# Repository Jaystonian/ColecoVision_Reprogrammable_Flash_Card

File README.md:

# ColecoVision_Reprogrammable_Flash_Card
An opensource, reprogrammable cartridge for the ColecoVision

MODES OF USE:

A) Single flash chip
- select 32KB or 16KB rom type (J1/JP1)
- select 80-BF for typical 16KB roms, or 80-FF for 32KB roms.
- 2nd flash chip must be absent and its jumpers may be ignored.

B) Dual flash chips (32KB double memory)
- select 16KB rom type (J1/JP1)
- One chip must select 80-BF and contain an array of the lower 16KB of each 32KB rom, the other must select C0-FF and contain the upper 16KB. 
- Your roms will need to be split in half for two 16KB binary files (low and high). Then concatenated into a low file and a high file, for writing.

**NOTES**
All modes require 32KB mode for re-programming flash chips.
Re-programming also requires SW2 switches to all be OPEN and
J2/JP2 must be PROG. Revert jumper back to USE when finished.
The re-programming adapter must have the pullups for block select and a
jumper to select which flash chip to reprogram.

While in 16KB mode, single or dual chip, Address 14 (A14) in SW2 
Memory Select will be included in selecting memory. 32KB mode will
require A14 and this jumper switch will be ignored by J1/JP1 configuration,
allowing the installation of a smaller DIP switch. If you use a single, smaller
Flash chip such as the SST39SF010A (instead of the 'F04) then you do not
need switches for A18 or A17, reducing it to two toggle switches for
four 32KB roms on A15 and A16.

Dual-flash uses dual 16KB for 32KB roms, so the A14 switch is needed to address roms.

8-12KB ROMs must be right-padded to 16KB with 0's.
20-24KB ROMs must be right-padded to 32KB with 0's.

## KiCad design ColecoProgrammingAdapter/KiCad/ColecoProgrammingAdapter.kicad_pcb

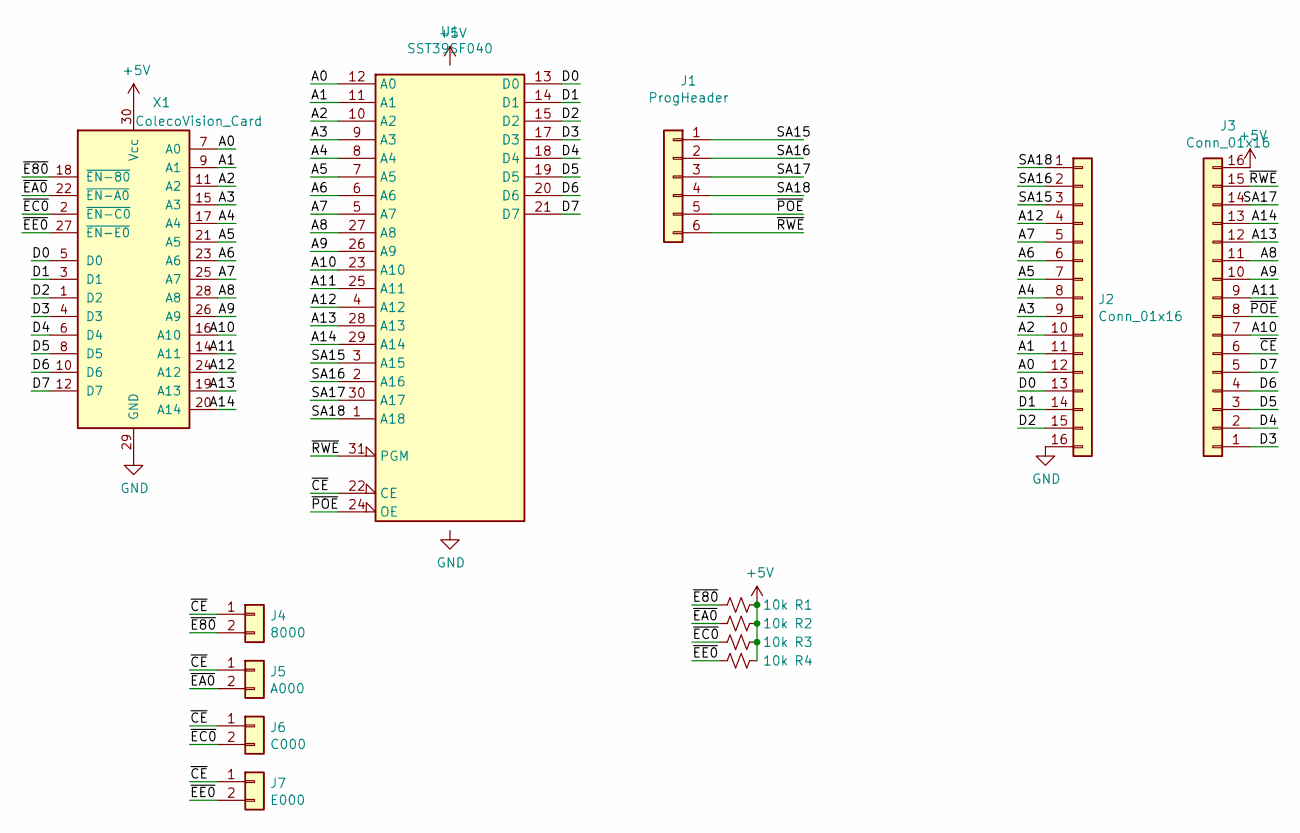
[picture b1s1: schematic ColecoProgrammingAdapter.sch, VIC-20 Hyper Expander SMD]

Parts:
J1: ProgHeader; PinSocket_1x06_P2.54mm_Vertical
J2, J3: Conn_01x16; PinHeader_1x16_P2.54mm_Vertical
J4: 8000; PinHeader_1x02_P2.54mm_Vertical
J5: A000; PinHeader_1x02_P2.54mm_Vertical
J6: C000; PinHeader_1x02_P2.54mm_Vertical
J7: E000; PinHeader_1x02_P2.54mm_Vertical
R1, R2, R3, R4: 10k; R_0805_2012Metric_Pad1.20x1.40mm_HandSolder
U1: SST39SF040; DIP-32_W15.24mm_Socket
X1: ColecoVision_Card; Coleco_CartridgeConnector

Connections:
+5V: J3.16, R1.1, R2.1, R3.1, R4.1, U1.32 (VCC), X1.30 (Vcc)
/A0: J2.12, U1.12 (A0), X1.7 (A0)
/A1: J2.11, U1.11 (A1), X1.9 (A1)
/A2: J2.10, U1.10 (A2), X1.11 (A2)
/A3: J2.9, U1.9 (A3), X1.15 (A3)
/A4: J2.8, U1.8 (A4), X1.17 (A4)
/A5: J2.7, U1.7 (A5), X1.21 (A5)
/A6: J2.6, U1.6 (A6), X1.23 (A6)
/A7: J2.5, U1.5 (A7), X1.25 (A7)
/A8: J3.11, U1.27 (A8), X1.28 (A8)
/A9: J3.10, U1.26 (A9), X1.26 (A9)
/A10: J3.7, U1.23 (A10), X1.16 (A10)
/A11: J3.9, U1.25 (A11), X1.14 (A11)
/A12: J2.4, U1.4 (A12), X1.24 (A12)
/A13: J3.12, U1.28 (A13), X1.19 (A13)
/A14: J3.13, U1.29 (A14), X1.20 (A14)
/D0: J2.13, U1.13 (D0), X1.5 (D0)
/D1: J2.14, U1.14 (D1), X1.3 (D1)
/D2: J2.15, U1.15 (D2), X1.1 (D2)
/D3: J3.1, U1.17 (D3), X1.4 (D3)
/D4: J3.2, U1.18 (D4), X1.6 (D4)
/D5: J3.3, U1.19 (D5), X1.8 (D5)
/D6: J3.4, U1.20 (D6), X1.10 (D6)
/D7: J3.5, U1.21 (D7), X1.12 (D7)
/SA15: J1.1, J2.3, U1.3 (A15)
/SA16: J1.2, J2.2, U1.2 (A16)
/SA17: J1.3, J3.14, U1.30 (A17)
/SA18: J1.4, J2.1, U1.1 (A18)
/~CE: J3.6, J4.1, J5.1, J6.1, J7.1, U1.22 (CE)
/~E80: J4.2, R1.2, X1.18 (~EN-80)
/~EA0: J5.2, R2.2, X1.22 (~EN-A0)
/~EC0: J6.2, R3.2, X1.2 (~EN-C0)
/~EE0: J7.2, R4.2, X1.27 (~EN-E0)
/~POE: J1.5, J3.8, U1.24 (OE)
/~RWE: J1.6, J3.15, U1.31 (PGM)
GND: J2.16, U1.16 (GND), X1.29 (GND)

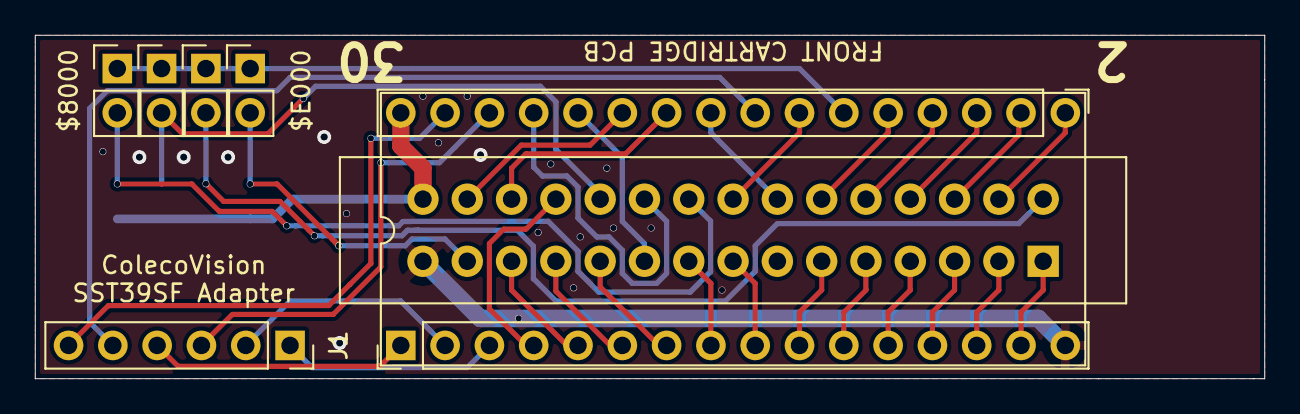
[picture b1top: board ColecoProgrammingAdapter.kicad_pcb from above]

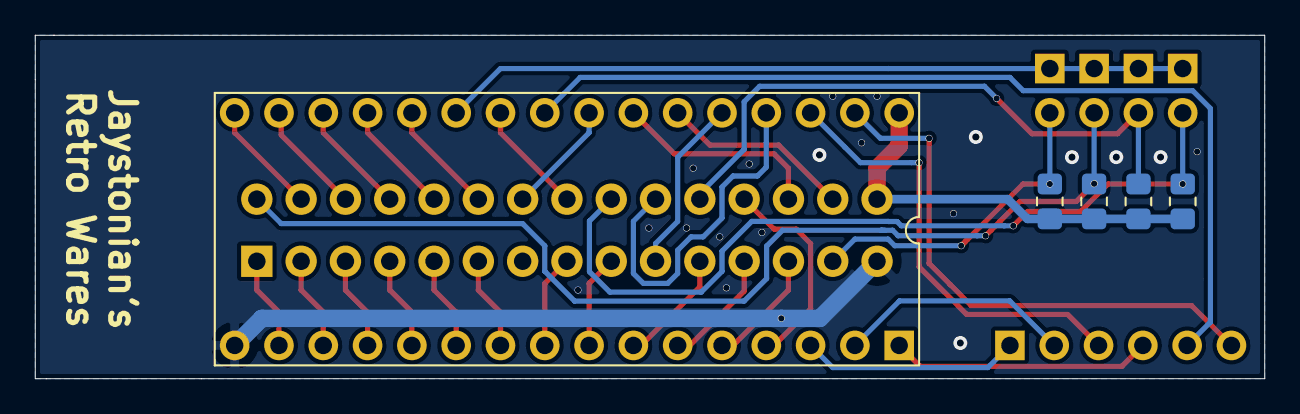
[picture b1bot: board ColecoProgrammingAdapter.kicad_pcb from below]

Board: 2 copper layers, 70.5 x 19.7 mm, 12 parts (5 on the bottom side), 36 nets.

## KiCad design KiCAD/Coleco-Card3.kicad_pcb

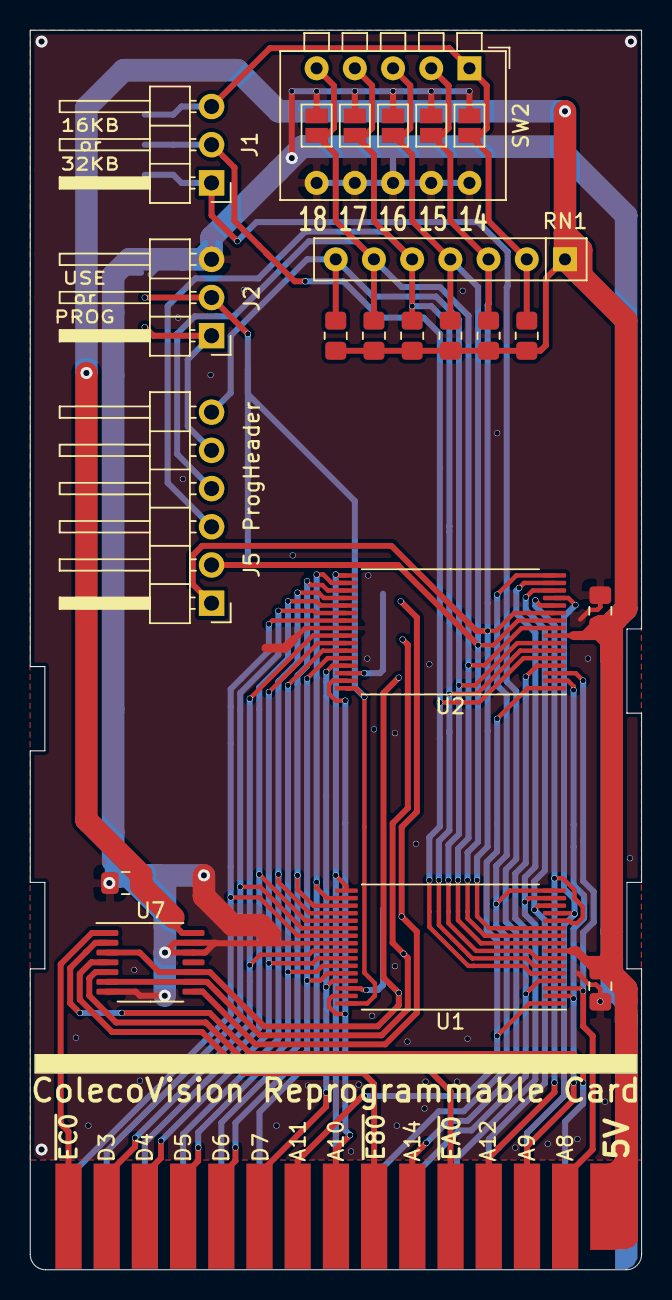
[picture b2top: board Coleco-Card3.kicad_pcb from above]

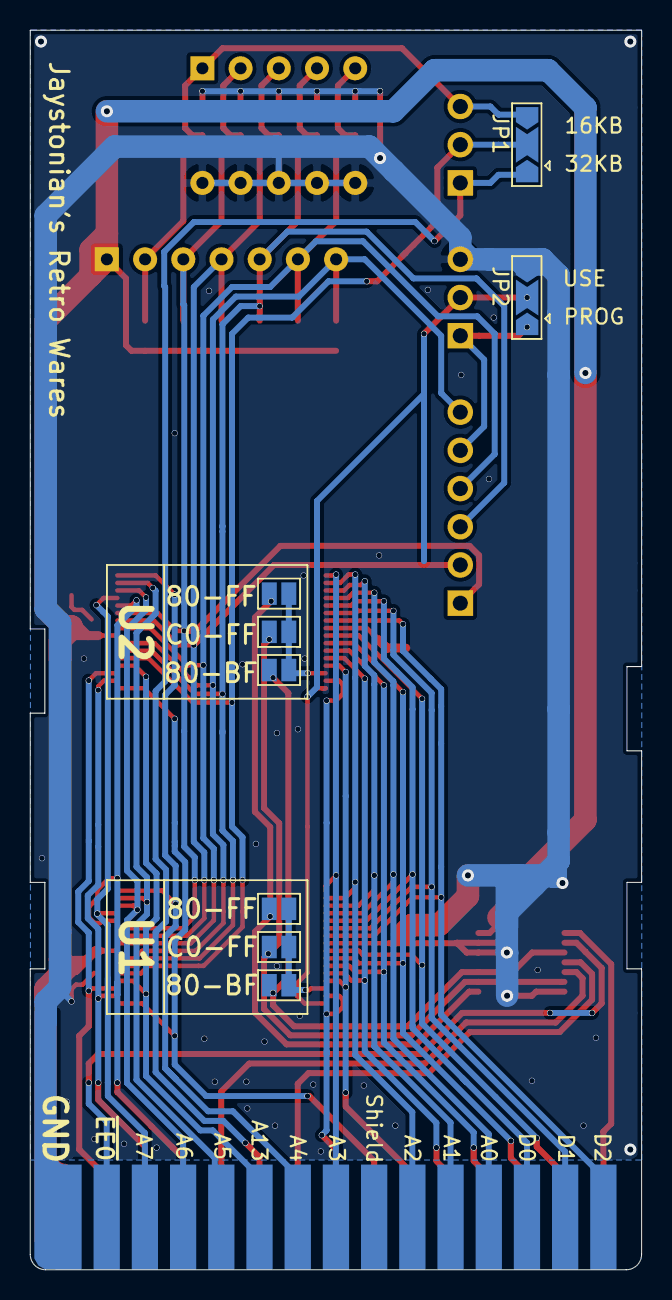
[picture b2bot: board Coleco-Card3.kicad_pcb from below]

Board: 2 copper layers, 40.6 x 82.4 mm, 31 parts (8 on the bottom side), 43 nets.

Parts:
C1, C2, C3: 0.1u; C_0805_2012Metric_Pad1.18x1.45mm_HandSolder
J1: 32KB_or_16KB; PinHeader_1x03_P2.54mm_Horizontal
J2: Prog_or_Use; PinHeader_1x03_P2.54mm_Horizontal
J5: Prog Header; PinHeader_1x06_P2.54mm_Horizontal
JP1: 32KB or 16KB; SolderJumper-3_P2.0mm_Open_TrianglePad1.0x1.5mm
JP2: Prog or Use; SolderJumper-3_P2.0mm_Open_TrianglePad1.0x1.5mm
JP3: SA14; SolderJumper-2_P1.3mm_Open_Pad1.0x1.5mm
JP4: SA15; SolderJumper-2_P1.3mm_Open_Pad1.0x1.5mm
JP5: SA16; SolderJumper-2_P1.3mm_Open_Pad1.0x1.5mm
JP6, JP14: SJE01; SolderJumper-2_P1.3mm_Open_Pad1.0x1.5mm
JP7, JP15: SJE23; SolderJumper-2_P1.3mm_Open_Pad1.0x1.5mm
JP8, JP16: SJEX; SolderJumper-2_P1.3mm_Open_Pad1.0x1.5mm
JP9: SA17; SolderJumper-2_P1.3mm_Open_Pad1.0x1.5mm
JP10: SA18; SolderJumper-2_P1.3mm_Open_Pad1.0x1.5mm
R1, R2, R3, R4, R5, R6: 10K; R_0805_2012Metric_Pad1.20x1.40mm_HandSolder
RN1: 10k; R_Array_SIP7
SW2: Memory Select; SW_DIP_SPSTx05_Piano_CTS_Series194-5MSTN_W7.62mm_P2.54mm
U1, U2: SST39SF040A-TSOP32; TSOP-32_14x8mm_P0.5mm
U7: 74LS08; TSSOP-14_4.4x5mm_P0.65mm
X1: CVS-Card; Coleco_Expansion_Card

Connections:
+5V: C1.1, C2.1, C3.1, R1.1, R2.1, R3.1, R4.1, R5.1, R6.1, RN1.1, U1.8, U2.8, U7.14, X1.30
/A0: U1.20, U2.20, X1.7
/A1: U1.19, U2.19, X1.9
/A2: U1.18, U2.18, X1.11
/A3: U1.17, U2.17, X1.15
/A4: U1.16, U2.16, X1.17
/A5: U1.15, U2.15, X1.21
/A6: U1.14, U2.14, X1.23
/A7: U1.13, U2.13, X1.25
/A8: U1.3, U2.3, X1.28
/A9: U1.2, U2.2, X1.26
/A10: U1.31, U2.31, X1.16
/A11: U1.1, U2.1, X1.14
/A12: U1.12, U2.12, X1.24
/A13: U1.4, U2.4, X1.19
/A14: J1.1, JP1.1, X1.20
/D0: U1.21, U2.21, X1.5
/D1: U1.22, U2.22, X1.3
/D2: U1.23, U2.23, X1.1
/D3: U1.25, U2.25, X1.4
/D4: U1.26, U2.26, X1.6
/D5: U1.27, U2.27, X1.8
/D6: U1.28, U2.28, X1.10
/D7: U1.29, U2.29, X1.12
/SA14: J1.3, JP1.3, JP3.1, R1.2, RN1.2, SW2.1
/SA15: J5.1, JP4.1, R2.2, RN1.3, SW2.2, U1.11, U2.11
/SA16: J5.2, JP5.1, R3.2, RN1.4, SW2.3, U1.10, U2.10
/SA17: J5.3, JP9.1, R4.2, RN1.5, SW2.4, U1.6, U2.6
/SA18: J5.4, JP10.1, R5.2, RN1.6, SW2.5, U1.9, U2.9
/XA14: J1.2, JP1.2, U1.5, U2.5
/~CE0: JP6.2, JP7.2, JP8.2, U1.30
/~CE1: JP14.2, JP15.2, JP16.2, U2.30
/~FCE0: U7.4, X1.18
/~FCE1: U7.5, X1.22
/~FCE01: JP6.1, JP14.1, U7.6, U7.9
/~FCE2: U7.1, X1.2
/~FCE3: U7.2, X1.27
/~FCE23: JP7.1, JP15.1, U7.3, U7.10
/~FCEX: JP8.1, JP16.1, U7.8
/~FOE: J2.2, JP2.2, U1.32, U2.32
/~POE: J2.1, J5.5, JP2.1
/~RWE: J5.6, R6.2, RN1.7, U1.7, U2.7
GND: C1.2, C2.2, C3.2, J2.3, JP2.3, JP3.2, JP4.2, JP5.2, JP9.2, JP10.2, SW2.6, SW2.7, SW2.8, SW2.9, SW2.10, U1.24, U2.24, U7.7, U7.12, U7.13, X1.29
